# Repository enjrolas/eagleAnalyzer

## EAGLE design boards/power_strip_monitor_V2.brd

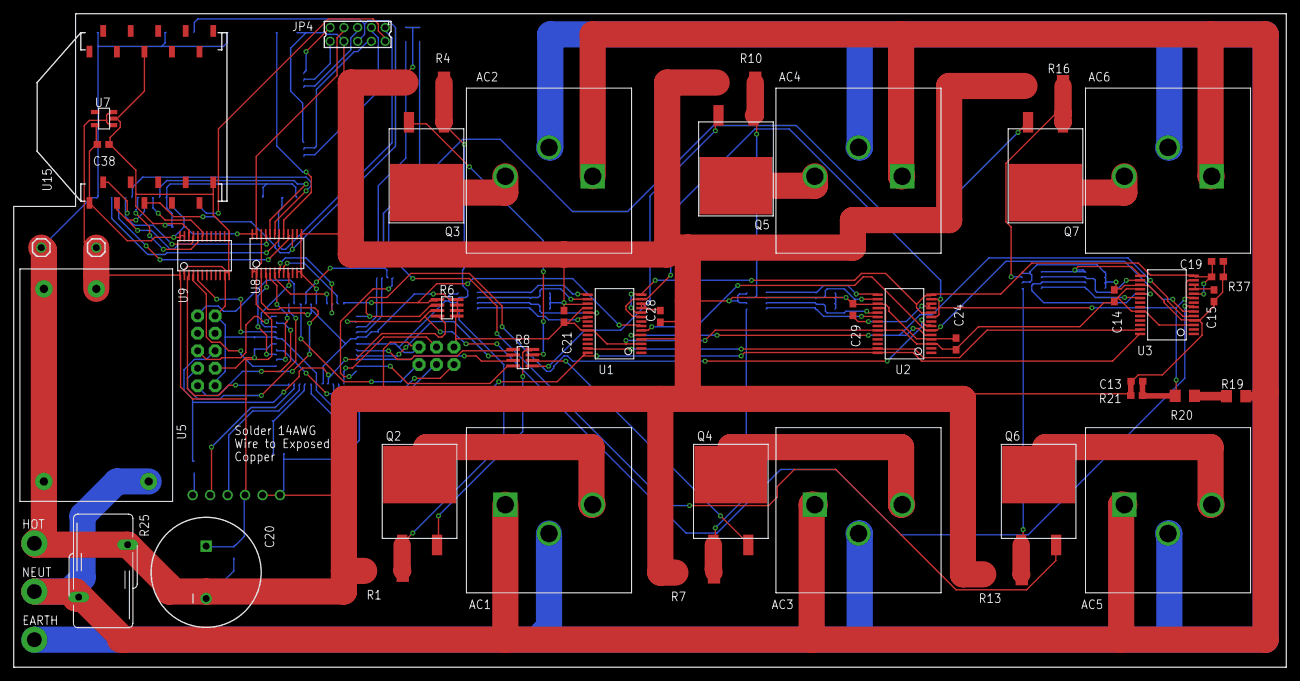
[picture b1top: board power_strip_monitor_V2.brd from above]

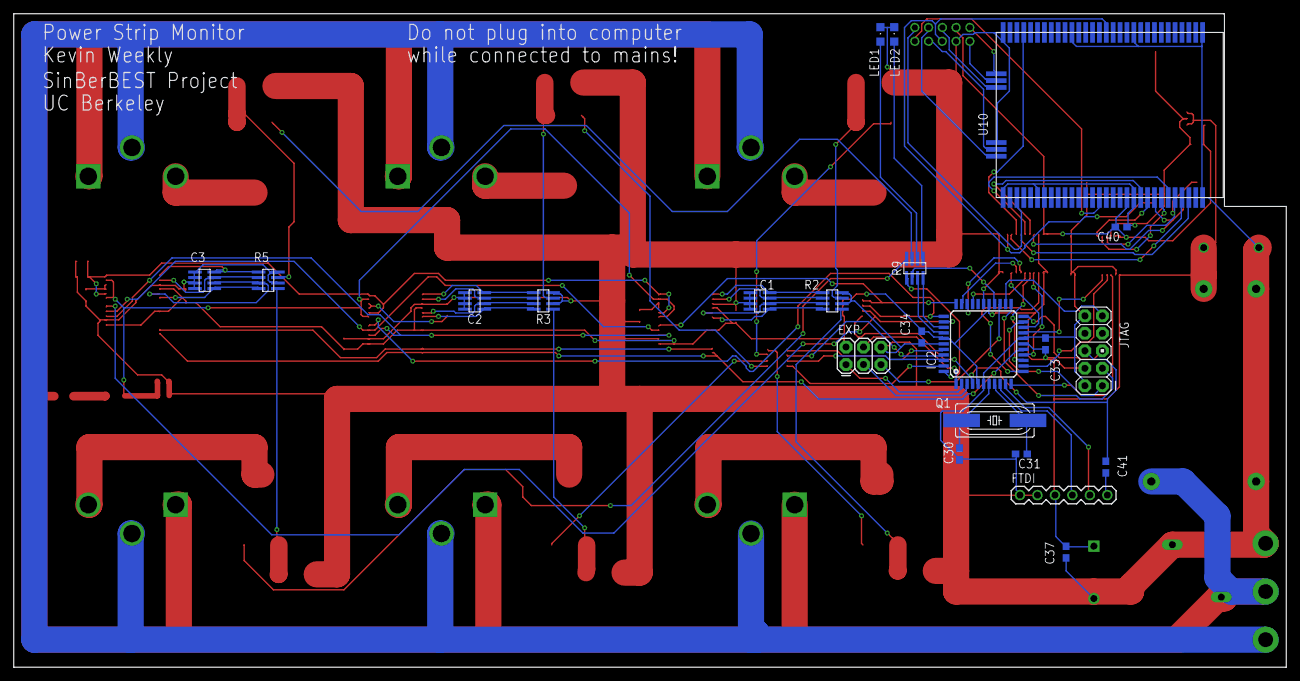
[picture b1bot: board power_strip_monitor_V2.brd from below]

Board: 4 copper layers, 185.0 x 95.0 mm, 71 parts (22 on the bottom side), 99 nets.

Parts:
AC1, AC2, AC3, AC4, AC5, AC6: AC_OUTLET; 3-213598-2
C1, C2, C3: 10n; 1206_NETWORK
C13, C19: 10n; 0603
C14, C15, C21, C24, C28, C29, C33, C34, C40, C41: .1u; 0603
C20: 1000uF 10V; CPOL-RADIAL-1000UF-63V
C30, C31: 22p; 0603
C37, C38: 10u; 0603
EARTH: 1P_HOLE; 14GAUGE_HOLE
EXP: EXP; 2X3
FTDI: 1X06
HOT: 1P_HOLE; 14GAUGE_HOLE
IC2: ATMEGA644A; TQFP44
JP4: 87758-1016
JTAG: JTAG; AVR_ICSP
LED1, LED2: CHIPLED_0805
NEUT: 1P_HOLE; 14GAUGE_HOLE
Q1: 16.384MHz; HC49UP
Q2, Q3, Q4, Q5, Q6, Q7: BTA312B-800E; D2PACK_NXP
R1, R4, R7, R10, R13, R16: 1m 1%; R2512
R2, R3, R5: 220 1%; 1206_NETWORK
R6: 10k; 1206_NETWORK
R8, R9: 100; 1206_NETWORK
R19, R20: 470k 200V; 1206
R21, R37: 1k 1%; 0603
R25: S14K680
TP21, TP24: TESTPOINT100MIL; TESTPOINT-100MIL
U1, U2, U3: CS5467; SSOP28L_CIRRUS
U5: RAC01_02-SC
U7: LT1761ES5-3.3; TSOT23-5_LINEAR
U8, U9: SN74LVC4245A; TSSOP24_TI
U10: LTP5901; LTP5901_MODULE
U15: XBEE-1B3; XBEE-SMD

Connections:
3.3V: C38.2, C40.2, JP4.7, U7.5, U8.23, U8.24, U9.23, U9.24, U10.55, U15.1
5V: C14.2, C20.1, C21.2, C24.2, C33.2, C34.2, C37.2, EXP.2, FTDI.3, IC2.5, IC2.17, IC2.27, IC2.38, JTAG.4, R6.A2, R6.B2, R6.C2, R6.D2, TP21.2, U1.3, U1.18, U1.23, U2.3, U2.18, U2.23, U3.3, U3.18, U3.23, U5.4, U7.1, U7.3, U8.1, U8.2, U8.22, U9.1
#CS1: IC2.33, R6.A1, U1.7
#CS2: IC2.34, R6.B1, U2.7
#CS3: IC2.35, R6.C1, U3.7
#CS_EXP: EXP.5, IC2.25
ATMEGA_TO_FTDI: FTDI.5, IC2.10
ATMEGA_TO_MOTE_3V: U8.21, U10.59, U15.3
ATMEGA_TO_MOTE_5V: IC2.12, U8.3
EARTH: AC1.3, AC2.3, AC3.3, AC4.3, AC5.3, AC6.3, EARTH.P$1
EXP_MISO: EXP.1, IC2.2
EXP_MOSI: EXP.4, IC2.1
EXP_SCK: EXP.3, IC2.3
FLASH_P_ENN: JP4.2, U10.51
FTDI_TO_ATMEGA: FTDI.4, IC2.9
GATE1: Q2.3, R8.A2
GATE2: Q3.3, R8.B2
GATE3: Q4.3, R8.C2
GATE4: Q5.3, R8.D2
GATE5: Q6.3, R9.A2
GATE6: Q7.3, R9.B2
GND: C1.A2, C1.B2, C1.C2, C1.D2, C2.A2, C2.B2, C2.C2, C2.D2, C3.A2, C3.B2, C3.C2, C3.D2, C13.2, C14.1, C15.1, C19.1, C20.2, C21.1, C24.1, C28.1, C29.1, C30.2, C31.2, C33.1, C34.1, C37.1, C38.1, C40.1, EXP.6, FTDI.1, FTDI.2, HOT.P$1, IC2.6, IC2.18, IC2.28, IC2.39, JP4.8, JTAG.2, JTAG.10, LED1.C, LED2.C, R1.1, R2.B1, R2.D1, R3.B1, R3.D1, R4.1, R5.B1, R5.D1, R7.1, R10.1, R13.1, R16.1, R21.2, R25.1, R37.1, TP24.2, U1.4, U1.17, U2.4, U2.17, U3.4, U3.17, U5.1, U5.3, U7.2, U8.11, U8.12, U8.13, U9.2, U9.11, U9.12, U9.13, U9.22, U10.1, U10.11, U10.20, U10.30, U10.34, U10.37, U10.42, U10.56, U10.66, U15.10, U15.16
HOT1: AC1.2, Q2.2
HOT2: AC2.2, Q3.2
HOT3: AC3.2, Q4.2
HOT4: AC4.2, Q5.2
HOT5: AC5.2, Q6.2
HOT6: AC6.2, Q7.2
HRET1: Q2.1, R1.2, R2.A1
HRET2: Q3.1, R2.C1, R4.2
HRET3: Q4.1, R3.A1, R7.2
HRET4: Q5.1, R3.C1, R10.2
HRET5: Q6.1, R5.A1, R13.2
HRET6: Q7.1, R5.C1, R16.2
I1+: C1.A1, R2.A2, U1.20
I1-: C1.B1, R2.B2, U1.19
I2+: C1.C1, R2.C2, U1.16
I2-: C1.D1, R2.D2, U1.15
I3+: C2.A1, R3.A2, U2.20
I3-: C2.B1, R3.B2, U2.19
I4+: C2.C1, R3.C2, U2.16
I4-: C2.D1, R3.D2, U2.15
I5+: C3.A1, R5.A2, U3.20
I5-: C3.B1, R5.B2, U3.19
I6+: C3.C1, R5.C2, U3.16
I6-: C3.D1, R5.D2, U3.15
IPCS_MISO: JP4.5, U10.33
IPCS_MOSI: JP4.4, U10.35
IPCS_SCK: JP4.3, U10.36
IPCS_SSN: JP4.1, U10.39
LED1: LED1.A, R9.C2
LED2: LED2.A, R9.D2
MISO: U1.6, U2.6, U3.6
MOSI: U1.27, U2.27, U3.27
MOTE_CLI_RX: JP4.10, U10.32
MOTE_CLI_TX: JP4.9, U10.31
MOTE_RADIO_INHIBIT_3V: U8.18, U10.64
MOTE_RADIO_INHIBIT_5V: IC2.30, U8.6
MOTE_RESETN_3V: JP4.6, U8.15, U10.15, U15.5
MOTE_RESETN_5V: IC2.20, U8.9
MOTE_RX_CTSN_3V: U9.19, U10.58
MOTE_RX_CTSN_5V: IC2.19, U9.5
MOTE_RX_RTSN_3V: U8.20, U10.57
MOTE_RX_RTSN_5V: IC2.15, U8.4
MOTE_SLEEPN_3V: U8.17, U10.27
MOTE_SLEEPN_5V: IC2.31, U8.7
MOTE_TIMEN_3V: U8.16, U10.63
MOTE_TIMEN_5V: IC2.32, U8.8
MOTE_TO_ATMEGA_3V: U9.21, U10.62, U15.2
MOTE_TO_ATMEGA_5V: IC2.11, U9.3
MOTE_TX_CTSN_3V: U8.19, U10.61
MOTE_TX_CTSN_5V: IC2.14, U8.5
MOTE_TX_RTSN_3V: U9.20, U10.60
MOTE_TX_RTSN_5V: IC2.13, U9.4
unnamed: C30.1, IC2.7, Q1.2
unnamed: R19.1, R20.1
unnamed: C31.1, IC2.8, Q1.1
unnamed: C15.2, U3.11, U3.12
unnamed: IC2.40, R8.A1
unnamed: IC2.41, R8.B1
unnamed: IC2.42, R8.C1
unnamed: IC2.43, R8.D1
unnamed: C29.2, U2.11, U2.12
unnamed: IC2.44, R9.A1
unnamed: IC2.26, R9.B1
unnamed: IC2.36, R9.D1
unnamed: C28.2, U1.11, U1.12
unnamed: IC2.37, R9.C1
NEUTRAL: AC1.1, AC2.1, AC3.1, AC4.1, AC5.1, AC6.1, NEUT.P$1, R19.2, R25.2, U5.2
RST: C41.1, IC2.4, JTAG.6, R6.D1
RTS#: C41.2, FTDI.6
SCLK: U1.5, U2.5, U3.5
TCK: IC2.21, JTAG.1
TDI: IC2.24, JTAG.9
TDO: IC2.23, JTAG.3
TMS: IC2.22, JTAG.5
V+: C13.1, R20.2, R21.1, U1.9, U1.13, U2.9, U2.13, U3.9, U3.13
V-: C19.2, R37.2, U1.10, U1.14, U2.10, U2.14, U3.10, U3.14
XIN: IC2.16, U1.28, U2.28, U3.28

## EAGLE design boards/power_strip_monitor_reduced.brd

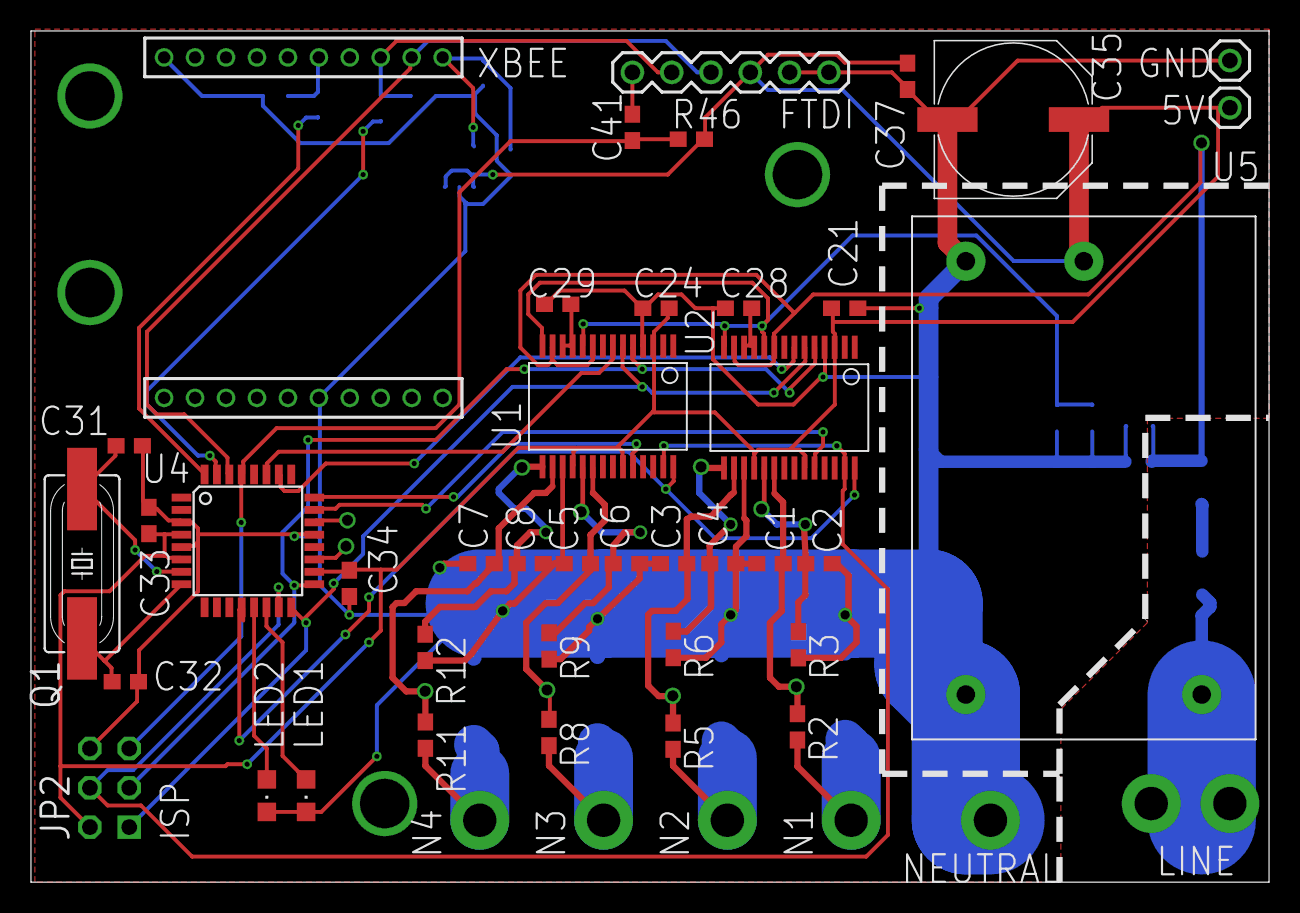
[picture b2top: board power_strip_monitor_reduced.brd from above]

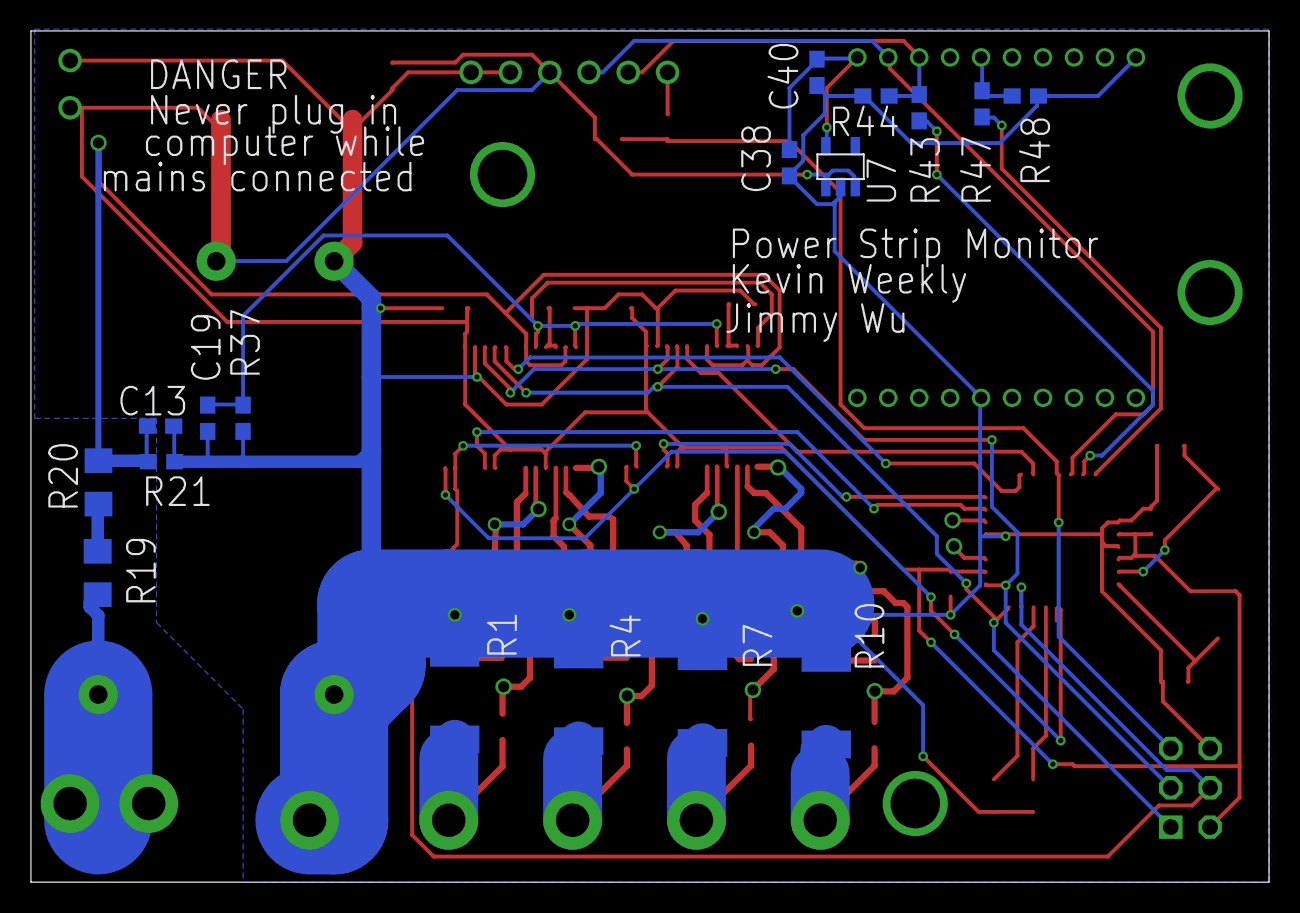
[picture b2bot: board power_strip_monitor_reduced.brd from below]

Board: 2 copper layers, 80.0 x 55.0 mm, 75 parts (17 on the bottom side), 42 nets.

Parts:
C1, C2, C3, C4, C5, C6, C7, C8, C13, C19: 10n; 0603
C21, C24, C28, C29, C33, C34, C40, C41: .1u; 0603
C31, C32: 22p; 0603
C35: 1000u; PANASONIC_G
C37, C38: 10u; 0603
JP1: 1X06
JP2: AVR_SPI_PRG_6NS; 2X3-NS
LED1, LED2: CHIPLED_0805
LINE, LINE1: 1P_HOLE; 14GAUGE_HOLE
N1, N2, N3, N4: 1P_HOLE; 14GAUGE_HOLE
NEUTRAL: 1P_HOLE; 14GAUGE_HOLE
Q1: 4.096MHz; HC49UP
R1, R4, R7, R10: 1m 1%; R2512
R2, R3, R5, R6, R8, R9, R11, R12: 330 1%; 0603
R19, R20: 470k 200V; 1206
R21, R37: 1k 1%; 0603
R43, R47: 4.7k; 0603
R44, R46, R48: 10k; 0603
TP1, TP2, TP3, TP4, TP5, TP6, TP7, TP8, TP18, TP19, TP20: TESTPOINTSMALLEST; TESTPOINT
TP21, TP24: TESTPOINT100MIL; TESTPOINT-100MIL
U1, U2: CS5467; SSOP28L_CIRRUS
U4: ATMEGA168; TQFP32-08
U5: RAC01_02-SC
U6: XBEE-1B1; XBEE-1
U7: TSOT23-5_LINEAR

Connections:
3.3V: C38.2, C40.2, U6.1, U7.5
5V: C21.2, C24.2, C33.2, C34.2, C35.+, C37.2, JP1.3, JP2.2, R46.2, TP21.2, U1.3, U1.18, U1.23, U2.3, U2.18, U2.23, U4.4, U4.6, U4.18, U5.4, U7.1, U7.3
#CS1: U2.7, U4.26
#CS2: U1.7, U4.27
#INT1: U2.24, U4.23
#INT2: U1.24, U4.24
ATMEGA_TO_XB: JP1.5, R43.2, R44.2, U6.3
GND: C1.2, C2.1, C3.2, C4.1, C5.2, C6.1, C7.2, C8.1, C13.2, C19.1, C21.1, C24.1, C28.1, C29.1, C31.2, C32.2, C33.1, C34.1, C35.-, C37.1, C38.1, C40.1, JP1.1, JP1.2, JP2.6, LED1.C, LED2.C, NEUTRAL.P$1, R1.1, R3.2, R4.1, R6.2, R7.1, R9.2, R10.1, R12.2, R21.2, R37.1, R44.1, R48.1, TP24.2, U1.4, U1.17, U2.4, U2.17, U4.3, U4.5, U4.21, U5.1, U5.3, U6.10, U6.16, U7.2
HOT: LINE.P$1, LINE1.P$1, R19.2, U5.2
I1+: C1.1, R2.1, TP2.P$1, U2.20
I1-: C2.2, R3.1, TP1.P$1, U2.19
I2+: C3.1, R5.1, TP3.P$1, U2.16
I2-: C4.2, R6.1, TP4.P$1, U2.15
I3+: C5.1, R8.1, TP5.P$1, U1.20
I3-: C6.2, R9.1, TP6.P$1, U1.19
I4+: C7.1, R11.1, TP7.P$1, U1.16
I4-: C8.2, R12.1, TP8.P$1, U1.15
MISO: JP2.1, U1.6, U2.6, U4.16
MOSI: JP2.4, U1.27, U2.27, U4.15
unnamed: LED2.A, U4.13
unnamed: R19.1, R20.1
unnamed: LED1.A, U4.14
unnamed: C29.2, U1.11, U1.12
unnamed: C28.2, U2.11, U2.12
unnamed: C31.1, Q1.2, U4.7
unnamed: C32.1, Q1.1, U4.8
unnamed: TP19.P$1, U4.19
unnamed: TP20.P$1, U4.22
unnamed: R43.1, U4.31
unnamed: R47.1, U4.32
NRET1: N1.P$1, R1.2, R2.2
NRET2: N2.P$1, R4.2, R5.2
NRET3: N3.P$1, R7.2, R8.2
NRET4: N4.P$1, R10.2, R11.2
RST: C41.1, JP2.5, R46.1, U4.29
RTS#: C41.2, JP1.6
SCLK: JP2.3, U1.5, U2.5, U4.17
V+: C13.1, R20.2, R21.1, TP18.P$1, U1.9, U1.13, U2.9, U2.13
V-: C19.2, R37.2, U1.10, U1.14, U2.10, U2.14
XB_RESET: R47.2, R48.2, U6.5
XB_TO_ATMEGA: JP1.4, U4.30, U6.2
XIN: U1.28, U2.28, U4.12

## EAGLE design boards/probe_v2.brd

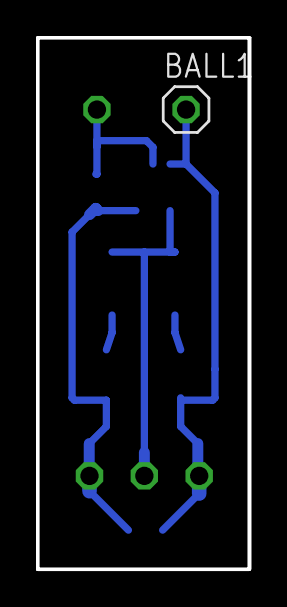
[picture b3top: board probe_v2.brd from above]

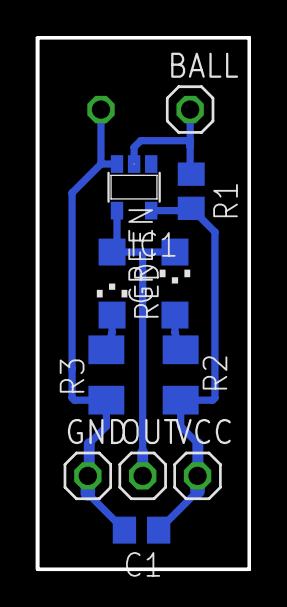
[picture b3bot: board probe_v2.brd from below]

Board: 2 copper layers, 11.7 x 29.5 mm, 12 parts (11 on the bottom side), 6 nets.

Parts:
BALL, BALL1: 1X01
C1: C0805
GND: 1X01
GREEN: CHIPLED_1206
IC1: 74AHC1G14DBV; SOT23-5
OUT: 1X01
R1: 1k; R0805
R2, R3: 330; M1206
RED: CHIPLED_1206
VCC: 1X01

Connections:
BALL: BALL.1, IC1.2, R1.1
GND: BALL1.1, C1.2, GND.1, IC1.3, R3.1
unnamed: GREEN.A, R2.1
unnamed: R3.2, RED.C
OUT: GREEN.C, IC1.4, OUT.1, RED.A
VCC: C1.1, IC1.5, R1.2, R2.2, VCC.1

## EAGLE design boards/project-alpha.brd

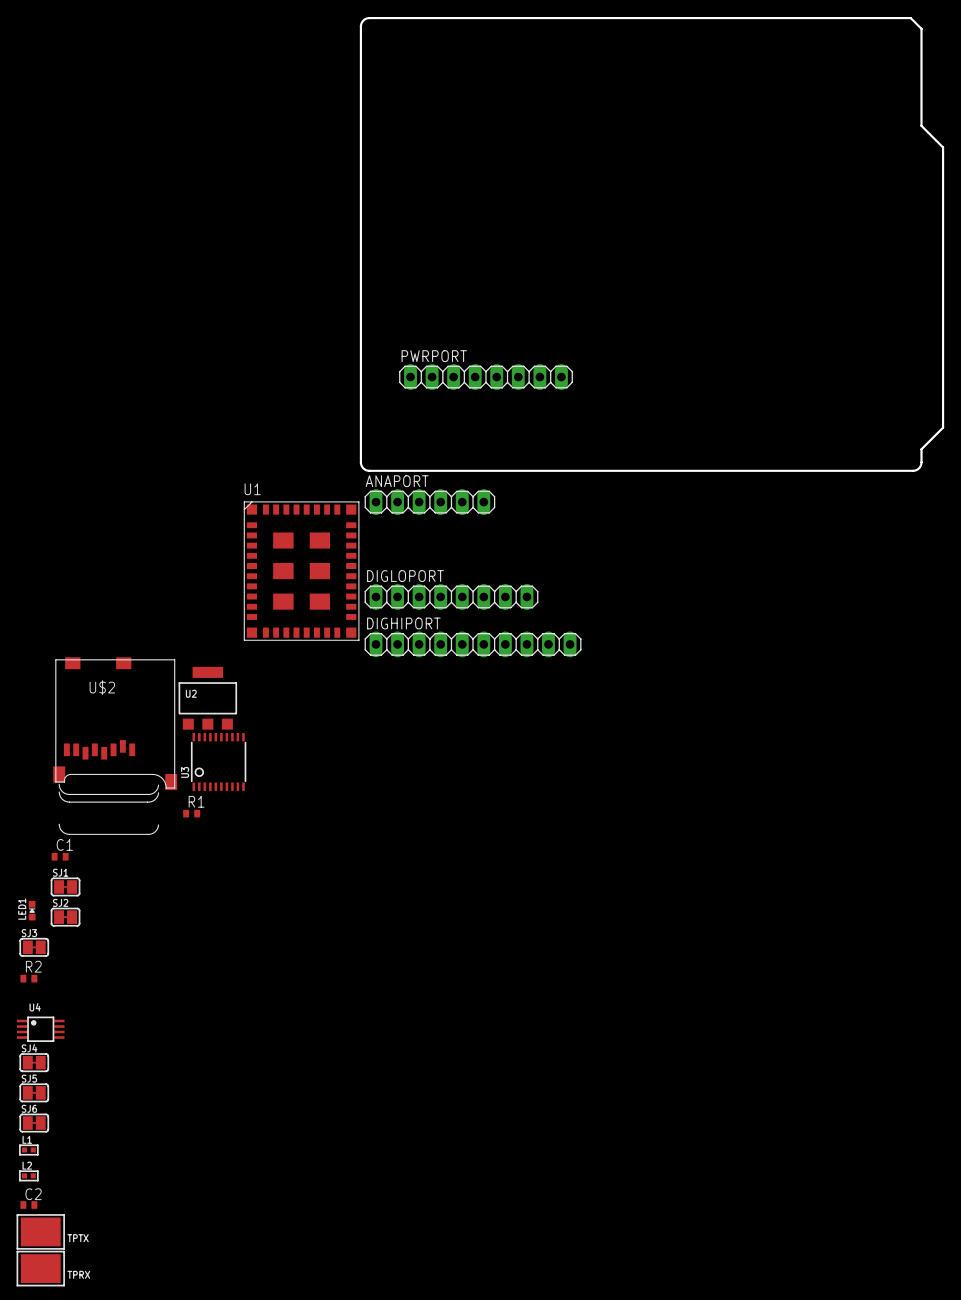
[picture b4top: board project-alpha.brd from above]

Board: 4 copper layers, 68.6 x 53.3 mm, 24 parts (0 on the bottom side), 34 nets, no tracks yet.

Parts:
ANAPORT: 1X06
C1, C2: C0402
DIGHIPORT: 1X10
DIGLOPORT: 1X08
L1, L2: _0402
LED1: CHIPLED_0603_NOOUTLINE
PWRPORT: 1X08
R1, R2: 0; R0402
SJ1, SJ2, SJ3, SJ4, SJ5, SJ6: SOLDERJUMPER_CLOSEDWIRE
TPRX: TESTPOINT_SMT
TPTX: TESTPOINT_SMT
U1: CC3000-MOD; CC3000-LGA
U2: TLV1117-33; SOT223-R
U3: TXS0108E; TSSOP20
U4: 24AA512; TSSOP8
U$2: MICROSD

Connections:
+3V3: PWRPORT.4, R1.1, R2.1, U1.23, U2.2, U3.2, U$2.4
+5V: U3.10, U3.19, U4.8
GND: L1.1, L2.1, PWRPORT.6, PWRPORT.7, SJ4.1, SJ5.1, SJ6.1, U1.1, U1.9, U1.10, U1.11, U1.16, U1.18, U1.20, U1.22, U1.25, U1.31, U1.32, U1.33, U1.34, U1.36, U1.37, U1.38, U1.39, U1.40, U1.41, U1.42, U1.43, U1.44, U1.45, U1.46, U2.1, U2.4, U3.11, U4.4, U4.7, U$2.6, U$2.MT1, U$2.MT2
unnamed: PWRPORT.5, U2.3
unnamed: U1.12, U3.1
unnamed: U1.17, U3.3, U$2.5
unnamed: U1.15, U3.4, U$2.3
unnamed: U1.13, U3.5, U$2.7
unnamed: U1.14, U3.6
unnamed: U1.26, U3.7
unnamed: C1.2, U1.35
unnamed: R1.2, U1.19
unnamed: C1.1, C2.1, L1.2
unnamed: DIGHIPORT.6, U3.16
unnamed: U1.27, U1.29
unnamed: U1.28, U1.30
unnamed: DIGHIPORT.7, U3.17
unnamed: DIGHIPORT.5, U3.18
unnamed: U3.8, U$2.2
unnamed: SJ1.1, U3.20
unnamed: DIGHIPORT.8, SJ1.2
unnamed: SJ2.1, U3.13
unnamed: DIGLOPORT.4, SJ2.2
unnamed: LED1.A, R2.2
unnamed: LED1.C, SJ3.1
unnamed: DIGLOPORT.5, SJ3.2
unnamed: SJ4.2, U4.1
unnamed: SJ5.2, U4.2
unnamed: SJ6.2, U4.3
unnamed: DIGHIPORT.1, U4.6
unnamed: DIGHIPORT.2, U4.5
unnamed: C2.2, L2.2
unnamed: TPTX.P$1, U1.6
unnamed: TPRX.P$1, U1.8

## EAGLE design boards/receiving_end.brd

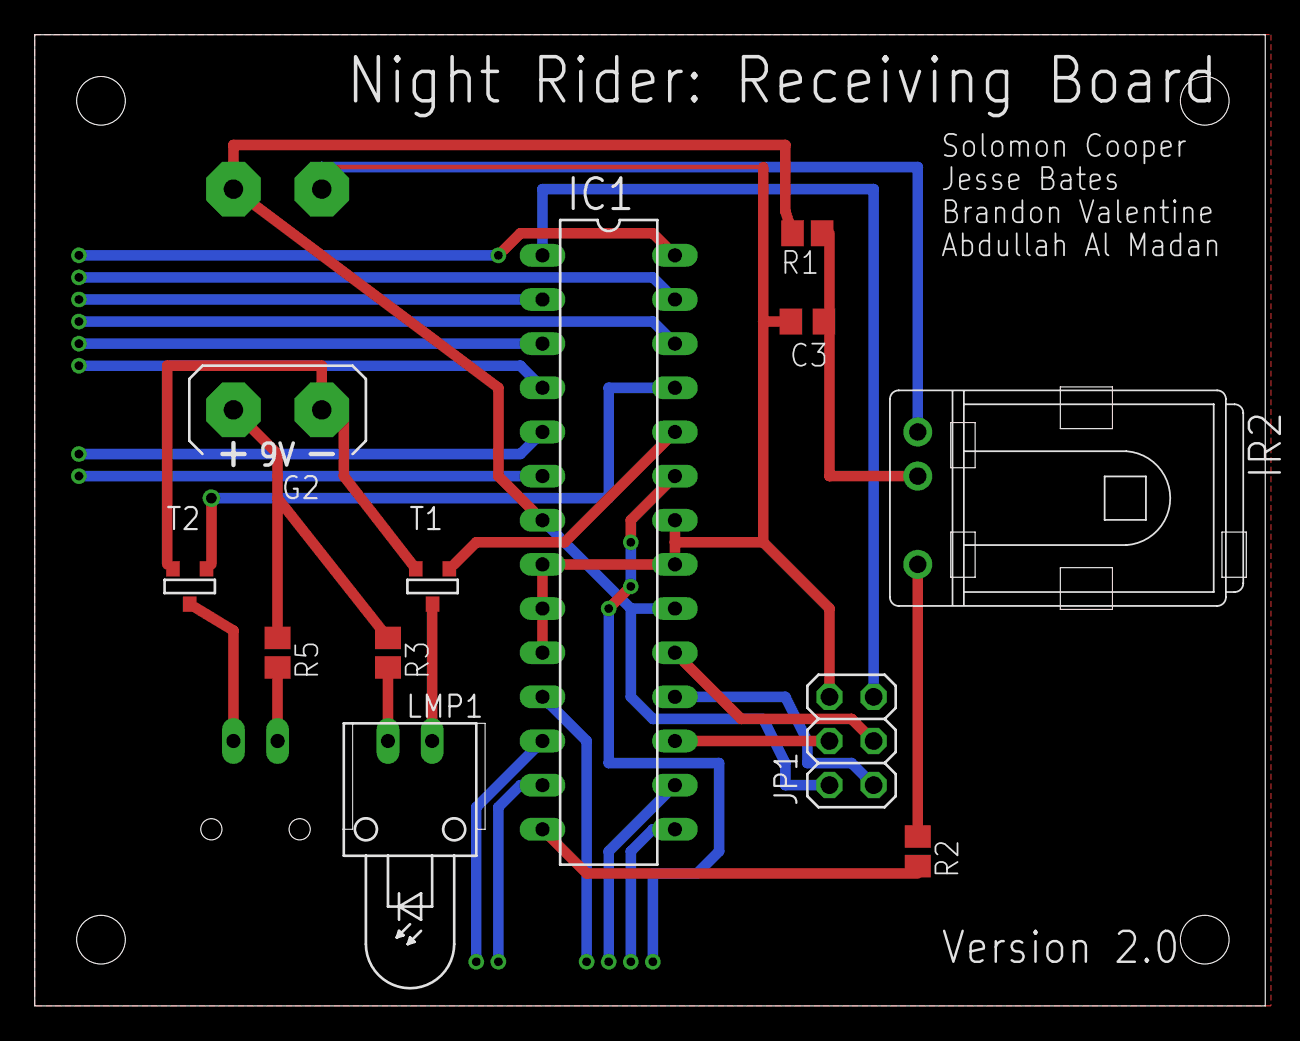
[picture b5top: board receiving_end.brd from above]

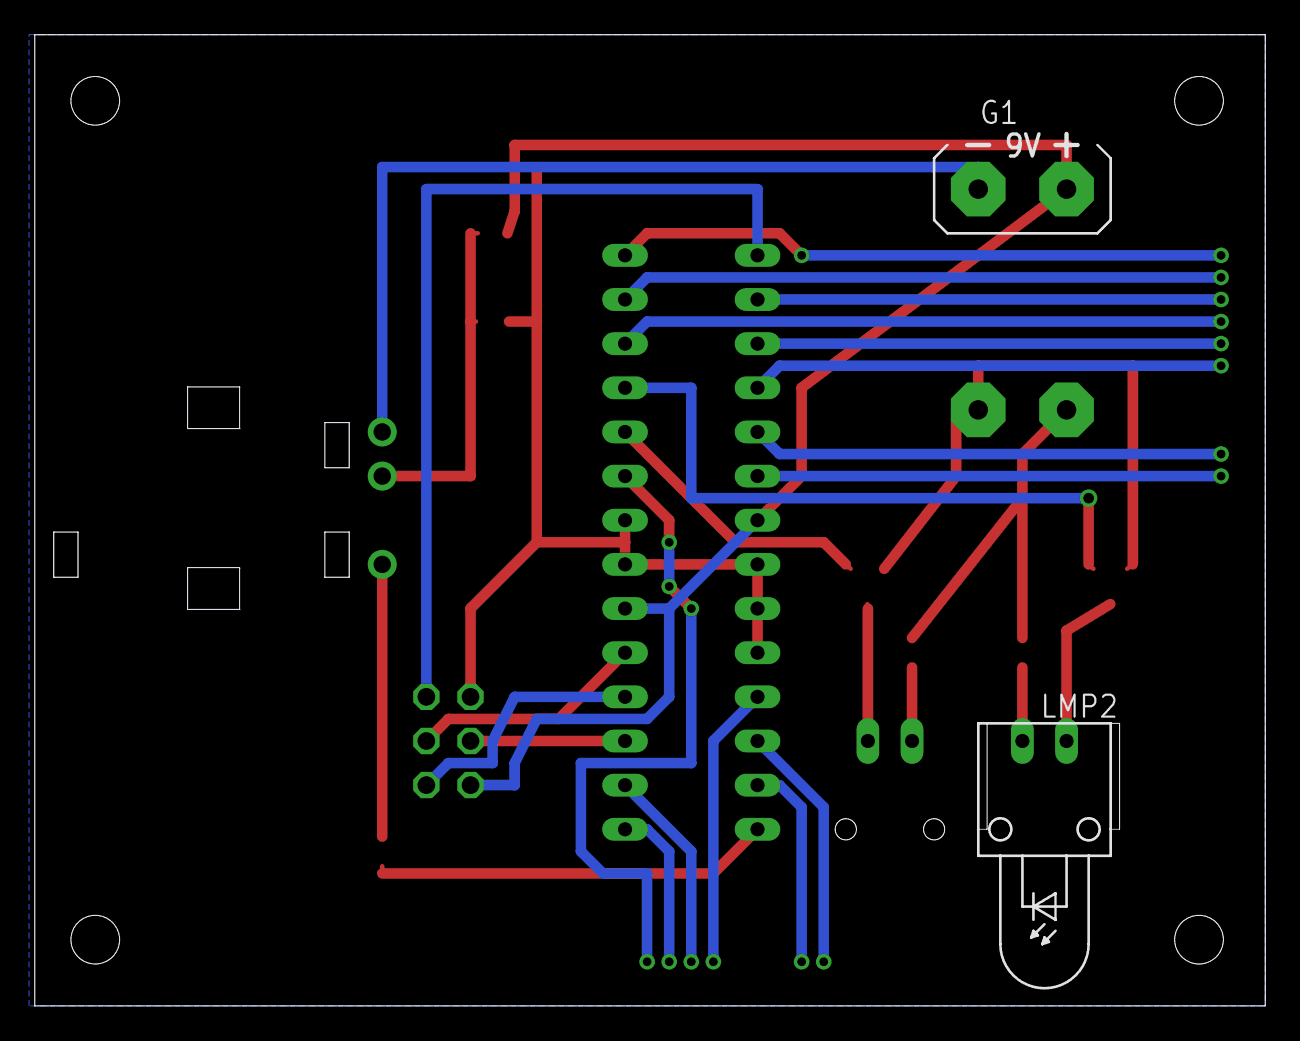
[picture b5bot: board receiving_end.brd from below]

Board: 2 copper layers, 70.8 x 55.9 mm, 14 parts (2 on the bottom side), 17 nets.

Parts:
C3: TBD; C0805
G1, G2: AB9V
IC1: MEGA8-P; DIL28-3
IR2: TSOP1756TB1; TSOP17_TB1
JP1: 2X03
LMP1, LMP2: LDH-5R
R1, R2: TBD; R0805
R3, R5: 0; R0805
T1, T2: SOT-23

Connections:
GND: C3.2, G1.-, IC1.8, IC1.9, IC1.10, IC1.21, IC1.22, IR2.GND, JP1.6
unnamed: IC1.25, T2.3
unnamed: IR2.VO, R2.1
unnamed: LMP1.1, T1.1
unnamed: LMP1.2, R3.2
unnamed: LMP2.1, T2.1
unnamed: G2.-, T1.2, T2.2
unnamed: G2.+, R3.1, R5.1
unnamed: LMP2.2, R5.2
unnamed: IC1.24, T1.3
unnamed: C3.1, IR2.VS, R1.1
unnamed: IC1.14, R2.2
unnamed: IC1.17, JP1.4
unnamed: IC1.18, JP1.1
unnamed: IC1.19, JP1.3
unnamed: IC1.1, JP1.5
VCC: G1.+, IC1.7, IC1.20, JP1.2, R1.2

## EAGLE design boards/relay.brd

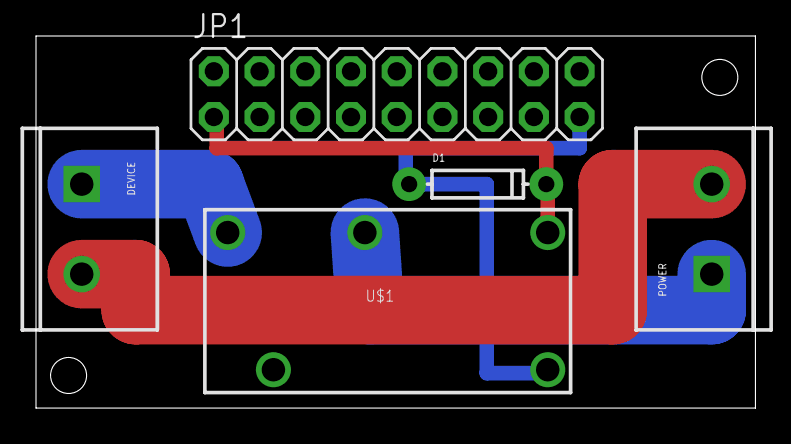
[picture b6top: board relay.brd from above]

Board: 2 copper layers, 40.0 x 20.7 mm, 5 parts (0 on the bottom side), 5 nets.

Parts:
D1: DIODE-1N4148
DEVICE: M025MM; SCREWTERMINAL-5MM-2
JP1: 2X09-BIG
POWER: M025MM; SCREWTERMINAL-5MM-2
U$1: RELAYPTH; RELAY-G5Q

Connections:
unnamed: D1.C, JP1.1, U$1.1
unnamed: D1.A, JP1.17, U$1.5
unnamed: POWER.1, U$1.2
unnamed: DEVICE.1, U$1.3
unnamed: DEVICE.2, POWER.2

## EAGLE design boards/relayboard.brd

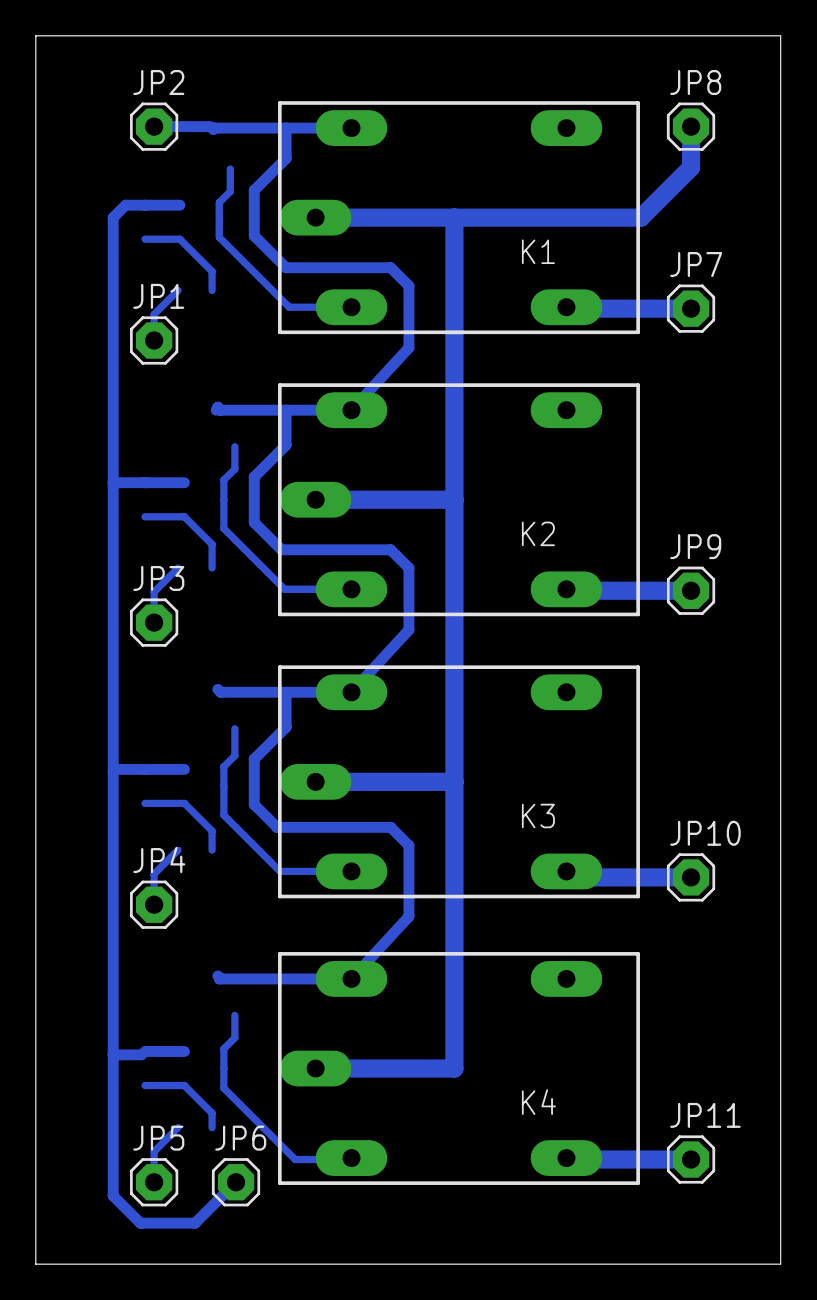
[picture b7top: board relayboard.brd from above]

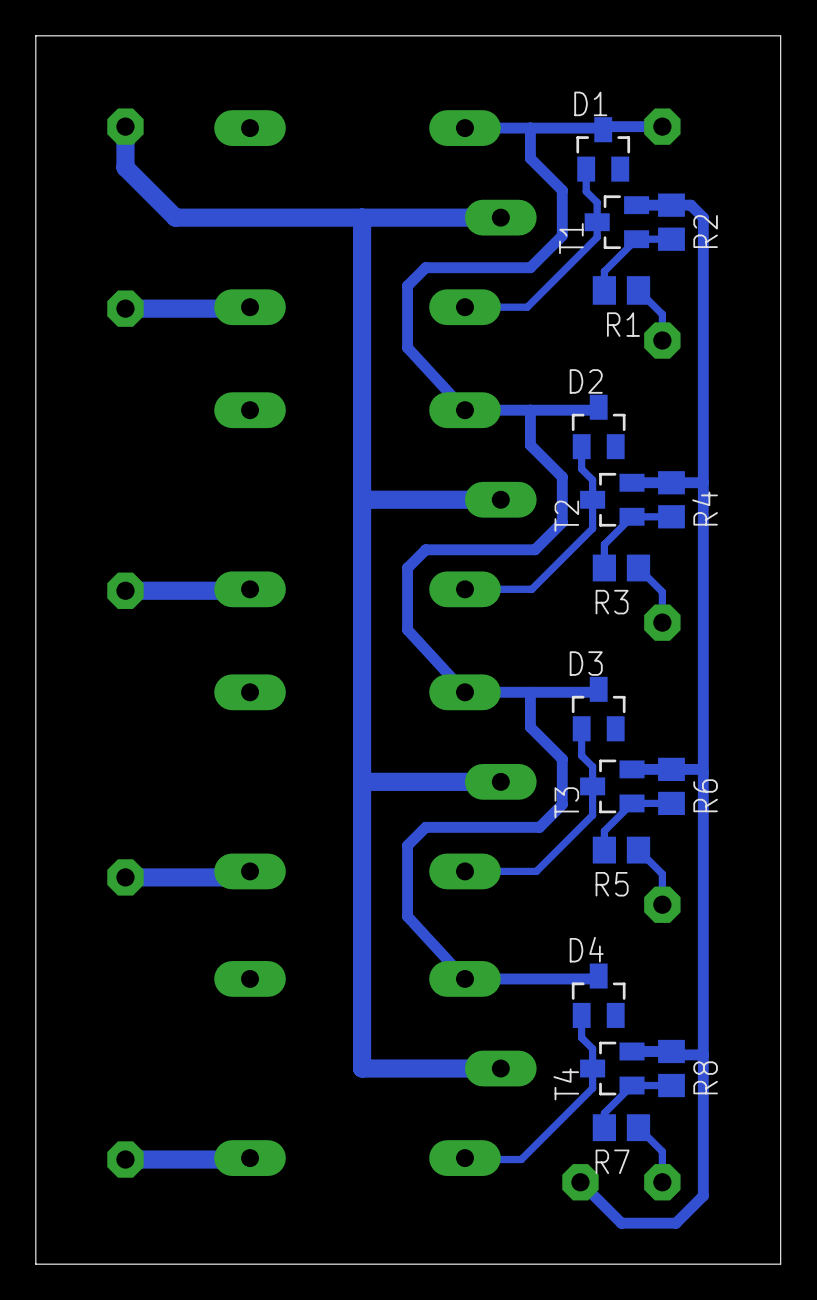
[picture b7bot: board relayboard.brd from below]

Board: 2 copper layers, 41.6 x 68.6 mm, 31 parts (16 on the bottom side), 19 nets.

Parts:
D1, D2, D3, D4: BAS16; SOT23
JP1, JP2, JP3, JP4, JP5, JP6, JP7, JP8, JP9, JP10, JP11: 1X01
K1, K2, K3, K4: 812H-1C-C; CQ1
R1: 10k; M0805
R2, R3, R4, R5, R6, R7, R8: 10k; R0805
T1, T2, T3, T4: IRLML2402; SOT23

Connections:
CH1: JP1.1, R1.1
CH2: JP3.1, R3.1
CH3: JP4.1, R5.1
CH4: JP5.1, R7.1
GND: JP6.1, R2.1, R4.1, R6.1, R8.1, T1.2, T2.2, T3.2, T4.2
unnamed: D1.1, K1.2, T1.3
unnamed: D2.1, K2.2, T2.3
unnamed: R1.2, R2.2, T1.1
unnamed: R3.2, R4.2, T2.1
unnamed: D3.1, K3.2, T3.3
unnamed: R5.2, R6.2, T3.1
unnamed: D4.1, K4.2, T4.3
unnamed: R7.2, R8.2, T4.1
unnamed: JP8.1, K1.C, K2.C, K3.C, K4.C
unnamed: JP7.1, K1.NO
unnamed: JP9.1, K2.NO
unnamed: JP10.1, K3.NO
unnamed: JP11.1, K4.NO
VCC: D1.3, D2.3, D3.3, D4.3, JP2.1, K1.1, K2.1, K3.1, K4.1

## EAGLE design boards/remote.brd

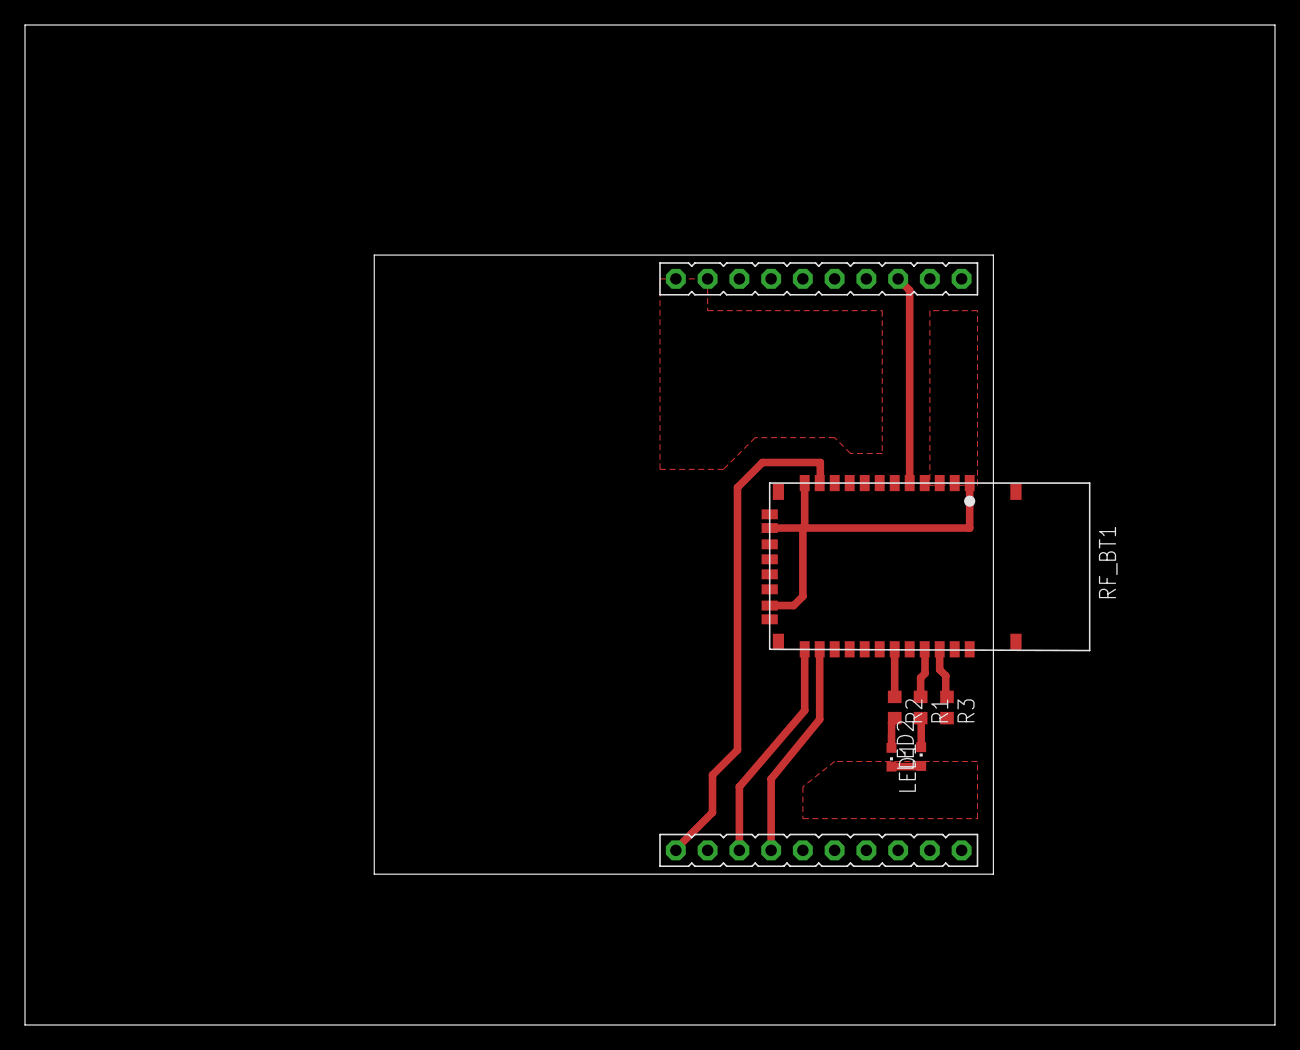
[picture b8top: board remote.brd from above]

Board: 2 copper layers, 100.0 x 80.0 mm, 7 parts (0 on the bottom side), 10 nets.

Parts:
LED1: CNCT; CHIPLED_0603
LED2: MODE; CHIPLED_0603
R1, R2: 220; R0603
R3: 0; R0603
RF_BT1: RN42BLUE; RN42_CUST_PAK
U$1: LAUNCHPAD-50MM-LEFT

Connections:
GND: LED1.C, LED2.A, RF_BT1.1, RF_BT1.12, RF_BT1.28, RF_BT1.29, U$1.GND
unnamed: R1.1, RF_BT1.21
unnamed: R2.1, RF_BT1.19
unnamed: LED2.C, R1.2
unnamed: LED1.A, R2.2
unnamed: R3.1, RF_BT1.22
RESET: RF_BT1.5, U$1.P2.5
RX: RF_BT1.13, U$1.P1.1
TX: RF_BT1.14, U$1.P1.2
VCC: R3.2, RF_BT1.11, U$1.VCC

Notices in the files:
parts and their libraries:
SparkFun-Passives: Licensing: CC v3.0 Share-Alike You are welcome to use this library for commercial purposes.
microbuilder: This work is placed in the public domain, and may be freely used for commercial and non-commercial work with the following conditions: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
